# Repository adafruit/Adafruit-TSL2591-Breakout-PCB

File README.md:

## Adafruit TSL2591 Breakout PCB
<a href="http://www.adafruit.com/products/1980"><br/>
<a href="http://www.adafruit.com/products/1980"><br/>
Click here to purchase one from the Adafruit shop</a>

When the future is dazzlingly-bright, this ultra-high-range luminosity sensor will help you measure it. The TSL2591 luminosity sensor is an advanced digital light sensor, ideal for use in a wide range of light situations. Compared to low cost CdS cells, this sensor is more precise, allowing for exact lux calculations and can be configured for different gain/timing ranges to detect light ranges from 188 uLux up to 88,000 Lux on the fly.

The best part of this sensor is that it contains both infrared and full spectrum diodes! That means you can separately measure infrared, full-spectrum or human-visible light. Most sensors can only detect one or the other, which does not accurately represent what human eyes see (since we cannot perceive the IR light that is detected by most photo diodes) This sensor is much like the TSL2561 but with a wider range (and the interface code is different). This sensor has a massive 600,000,000:1 dynamic range! Unlike the TSL2561 you cannot change the I2C address, so keep that in mind.

The built in ADC means you can use this with any microcontroller, even if it doesn't have analog inputs. The current draw is extremely low, so its great for low power data-logging systems. about 0.4mA when actively sensing, and less than 5 uA when in power-down mode.

PCB files for the Adafruit TSL2591 Breakout PCB. The format is EagleCAD schematic and board layout
- https://www.adafruit.com/product/1980

### License

Adafruit invests time and resources providing this open source design, please support Adafruit and open-source hardware by purchasing products from [Adafruit](https://www.adafruit.com)!

All text above must be included in any redistribution

Designed by Limor Fried/Ladyada for Adafruit Industries.
Creative Commons Attribution/Share-Alike, all text above must be included in any redistribution. 
See license.txt for additional information.

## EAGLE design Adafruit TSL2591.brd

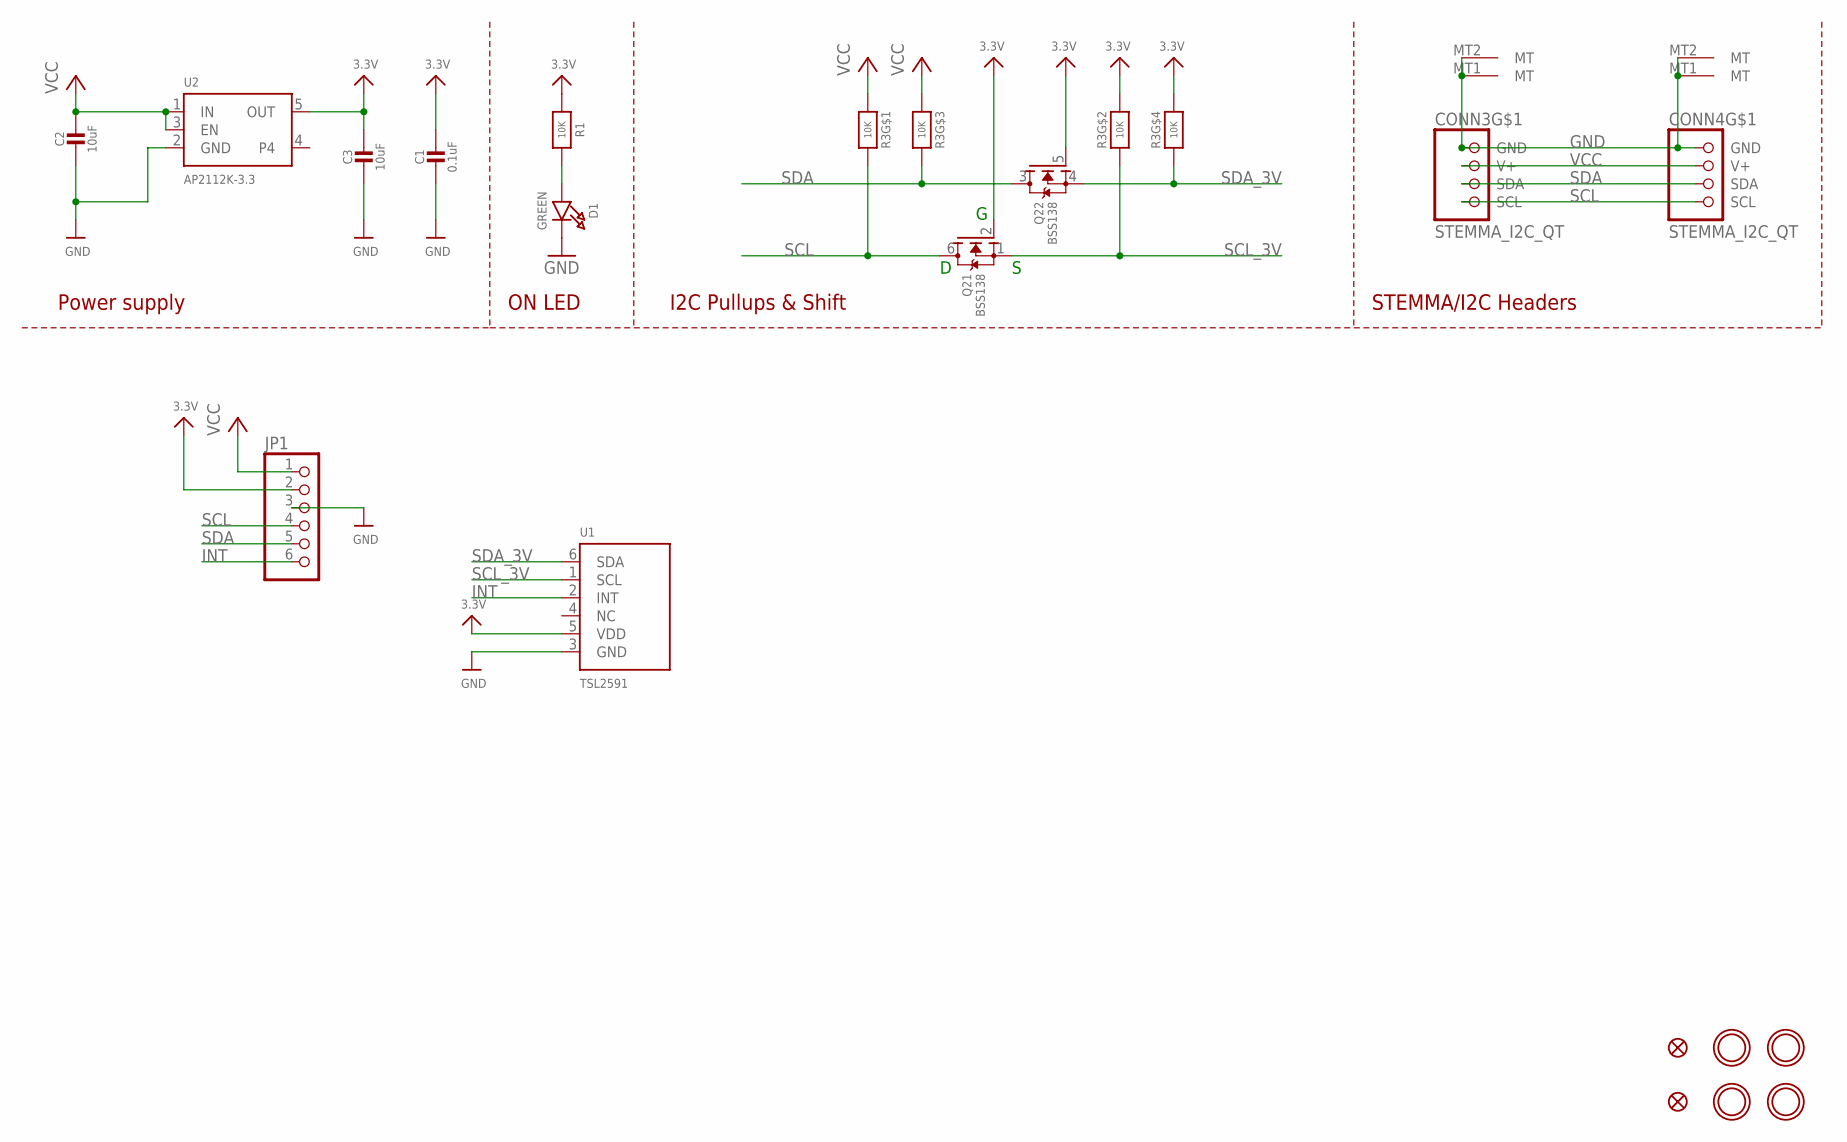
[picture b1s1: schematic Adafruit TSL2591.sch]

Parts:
C1: 0.1uF; 0603-NO
C2, C3: 10uF; 0805-NO
CONN3, CONN4: STEMMA_I2C_QT; JST_SH4
D1: GREEN; CHIPLED_0603_NOOUTLINE
FID3, FID4: FIDUCIAL_1MM
JP1: HEADER-1X670MIL; 1X06_ROUND_70
Q2: BSS138; SOT363
R1: 10K; 0603-NO
R3: 10K; RESPACK_4X0603
U1: TSL2591; DFN6_TAOS
U2: AP2112K-3.3; SOT23-5
U$1, U$17, U$19, U$21: MOUNTINGHOLE2.5; MOUNTINGHOLE_2.5_PLATED

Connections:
3.3V: C1.1, C3.1, JP1.2, Q2.2 (G), Q2.5 (G), R1.1, R3.2 (1), R3.4 (1), U1.5 (VDD), U2.5 (OUT)
GND: C1.2, C2.2, C3.2, CONN3.1 (GND), CONN3.MT1 (MT), CONN3.MT2 (MT), CONN4.1 (GND), CONN4.MT1 (MT), CONN4.MT2 (MT), D1.C, JP1.3, U1.3 (GND), U2.2 (GND)
INT: JP1.6, U1.2 (INT)
unnamed: D1.A, R1.2
SCL: CONN3.4 (SCL), CONN4.4 (SCL), JP1.4, Q2.6 (D), R3.8 (2)
SCL_3V: Q2.1 (S), R3.7 (2), U1.1 (SCL)
SDA: CONN3.3 (SDA), CONN4.3 (SDA), JP1.5, Q2.3 (D), R3.6 (2)
SDA_3V: Q2.4 (S), R3.5 (2), U1.6 (SDA)
VCC: C2.1, CONN3.2 (V+), CONN4.2 (V+), JP1.1, R3.1, R3.3 (1), U2.1 (IN), U2.3 (EN)

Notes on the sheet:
I2C Pullups & Shift
STEMMA/I2C Headers
ON LED
Power supply

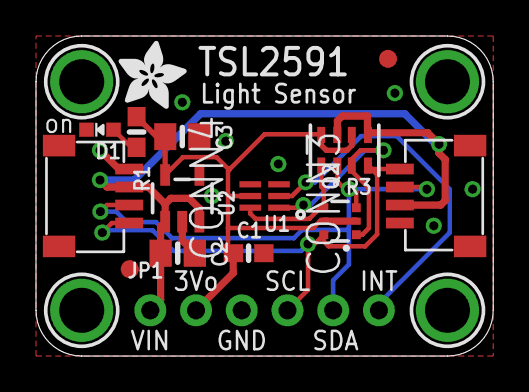
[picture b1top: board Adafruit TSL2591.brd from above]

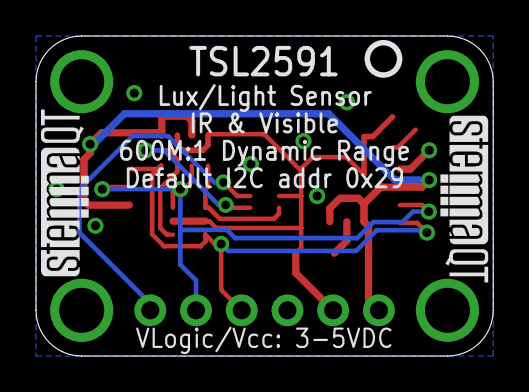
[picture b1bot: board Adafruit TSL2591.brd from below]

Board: 2 copper layers, 25.4 x 17.8 mm, 22 parts (3 on the bottom side), 9 nets.

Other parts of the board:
U$22: ADAFRUIT_3.5MM
U$25: PCBFEAT-REV-040
U$30, U$31: STEMMAQT

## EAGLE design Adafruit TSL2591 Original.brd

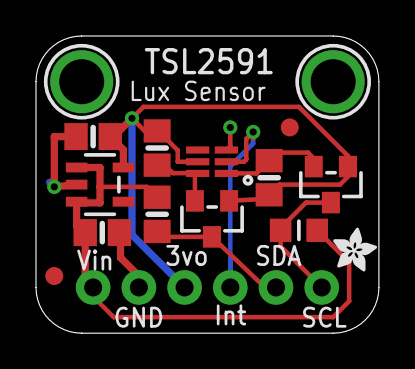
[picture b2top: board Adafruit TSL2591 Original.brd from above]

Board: 2 copper layers, 19.1 x 16.5 mm, 17 parts (1 on the bottom side), 8 nets.

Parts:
C2, C3: 10uF; 0805-NO
FID1, FID2: FIDUCIAL""; FIDUCIAL_1MM
JP1: 1X06_ROUND_FULL_76
Q1, Q2: BSS138; SOT23-WIDE
R2, R3, R4: 10K; 0805-NO
R5: 10K; _0805MP
U1: TSL2591; DFN6_TAOS
U2: MIC5225-3.3; SOT23-5
U$15: ADAFRUIT_2.5MM
U$18, U$19: MOUNTINGHOLE2.5; MOUNTINGHOLE_2.5_PLATED
U$20: ADAFRUIT_5MM

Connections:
3.3V: C3.1, JP1.3, Q1.1, Q2.1, R2.2, R3.2, U1.5, U2.5
GND: C2.2, C3.2, JP1.2, U1.3, U2.2
INT: JP1.4, U1.2
SCL: JP1.6, Q2.3, R5.1
SCL_3V: Q2.2, R3.1, U1.1
SDA: JP1.5, Q1.3, R4.1
SDA_3V: Q1.2, R2.1, U1.6
VIN: C2.1, JP1.1, R4.2, R5.2, U2.1, U2.3

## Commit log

2016-08-17 init
2020-09-29 Rename.
2020-09-29 Rename
2020-09-29 Add image.
2020-09-29 add board files.

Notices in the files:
parts and their libraries:
microbuilder: This work is placed in the public domain, and may be freely used for commercial and non-commercial work with the following conditions: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
